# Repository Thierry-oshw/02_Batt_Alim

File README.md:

# 02_Batt_Alim

Le module Batt_Alim permet de gérer la charge d'une batterie Lipo constituée d'une seule cellule (4.2V) à partir d'une source de type 5V USB.
Il permet aussi de récupérer cette tension batterie variable et de reconstituer un 5V constant grâce à un DCDC.

La licence est celle du CERN Open Hardware Licence version 2; CERN-OHL-P ; permissive.
Le fichier de cette license est présent dans le répertoire: cern_ohl_p_v2.txt

# Photos

Ci-joint la photo de la version de 2021_06_04 // Here picture of version 2021_06_04:

# Schéma et fonctionnement

Ci-joint le schéma de la version de 2021_06_04 // Here schematic of version 2021_06_04:

Le module fonctionne de la façon suivante:
Il faut l'alimenter avec une tension 5V +-5% (typiquement celle de l'USB classique) sur la pin Vext. (Ne pas oublier GND bien sûr).

Il faut brancher la batterie Lipo sur V_bat+ et GND. La batterie Lipo doit être constituée d'une seule cellule, qui doit être chargée à 4.2V, présente une tension de 3.7V typique, et dont la tension de mise en protection est de 3V. La résistance R7 de 10kOhms permet de régler la puce TP4056 sur un courant de charge de 130mA. La batterie Lipo doit donc avoir une capacité d'au moins 2*130mAh, soit 260mAh au minimum. Plus d'information sur www.tp4056.com.

La sortie V_sum est à relier à DCDC_IN (ceci permet d'insérer un interrupteur à cet endroit).

La sortie 5V_p est une tension issue du DCDC qui est filtrée et protégée par la diode D1 et le condensateur C5.

La LED D6 indique la présence de 5V à la sortie du DCDC, avec "5V ON" comme étiquette.

Les LEDs D2 et D3 indiquent respectivement la charge et le mode standby du TP4056. Les étiquettes sont "CHG" et "STBY".

# Archives:

Ci-joint la photo de la version de 2020_12_22 // Here picture of version 2020_12_22:

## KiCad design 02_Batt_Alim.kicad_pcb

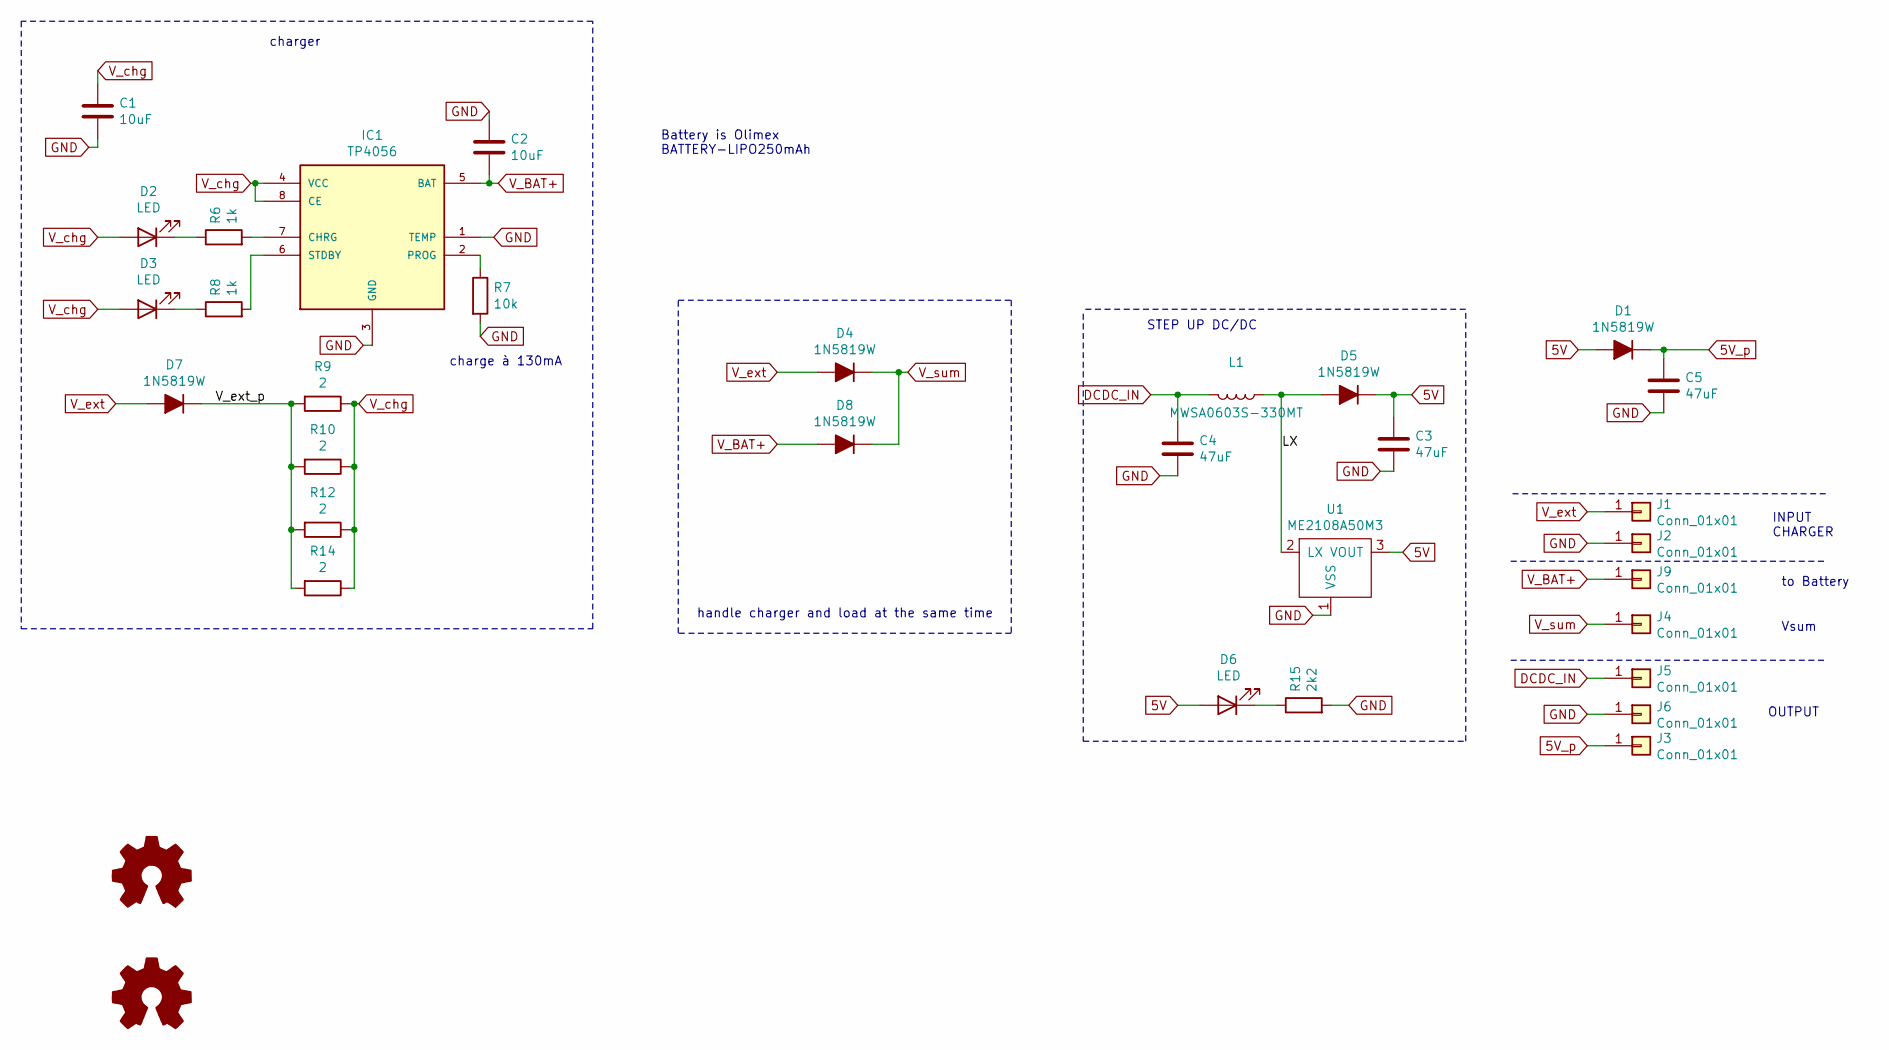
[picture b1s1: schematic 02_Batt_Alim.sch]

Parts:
C1, C2: 10uF; C_0603_1608Metric
C3, C4, C5: 47uF; C_1210_3225Metric
D1, D4, D5, D7, D8: 1N5819W; D_SOD-123F
D2, D3, D6: LED; D_0603_1608Metric
IC1: TP4056; SOP-8
J1, J2, J3, J4, J5, J6, J9: Conn_01x01; Castellated_conn
L1: MWSA0603S-330MT; L_Sunlord_MWSA0603S_6.6x7.0x2.8mm
R6, R8: 1k; R_0603_1608Metric
R7: 10k; R_0603_1608Metric
R9, R10, R12, R14: 2; R_0603_1608Metric
R15: 2k2; R_0603_1608Metric
U1: ME2108A50M3; SOT-23_Handsoldering

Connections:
5V: C3.1, D1.2 (A), D5.1 (K), D6.2 (A), U1.3 (VOUT)
5V_p: C5.1, D1.1 (K), J3.1
/LX: D5.2 (A), L1.1, U1.2 (LX)
/V_ext_p: D7.1 (K), R9.2, R10.2, R12.2, R14.2
DCDC_IN: C4.1, J5.1, L1.2
GND: C1.2, C2.1, C3.2, C4.2, C5.2, IC1.1 (TEMP), IC1.3 (GND), J2.1, J6.1, R7.2, R15.2, U1.1 (VSS)
unnamed: D2.1 (K), R6.1
unnamed: D3.1 (K), R8.1
unnamed: D6.1 (K), R15.1
unnamed: IC1.2 (PROG), R7.1
unnamed: IC1.6 (STDBY), R8.2
unnamed: IC1.7 (CHRG), R6.2
V_BAT+: C2.2, D8.2 (A), IC1.5 (BAT), J9.1
V_chg: C1.1, D2.2 (A), D3.2 (A), IC1.4 (VCC), IC1.8 (CE), R9.1, R10.1, R12.1, R14.1
V_ext: D4.2 (A), D7.2 (A), J1.1
V_sum: D4.1 (K), D8.1 (K), J4.1

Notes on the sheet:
Battery is Olimex BATTERY-LIPO250mAh
INPUT CHARGER
OUTPUT
STEP UP DC/DC
handle charger and load at the same time
charger
charge à 130mA
to Battery
Vsum

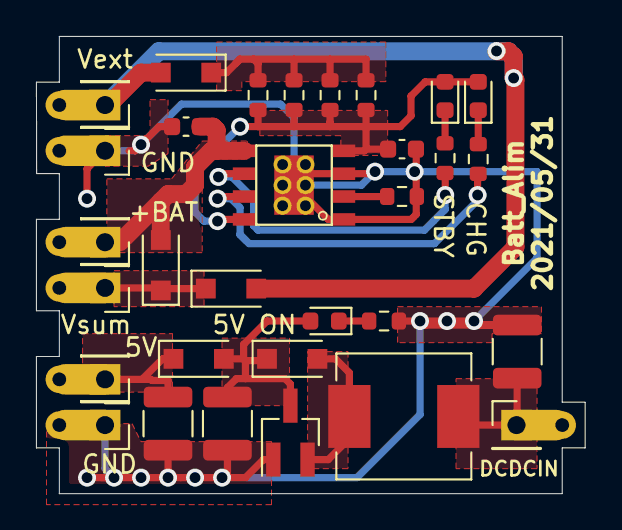
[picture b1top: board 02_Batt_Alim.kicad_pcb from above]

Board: 2 copper layers, 30.5 x 25.4 mm, 31 parts (0 on the bottom side), 16 nets.

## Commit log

2020-12-06 gitignore set to kicad version
2020-12-13 saisie du schéma + placement + premier routage
2020-12-14 dernières modification et routage avec plan de cuivre
2020-12-16 corrected diodes schematics; gerbers generation
2020-12-16 added kicad et oshw logos
2020-12-19 ajout logo kicad
2020-12-22 routage
2021-01-28 added picture
2021-02-06 simplify!
    1) battery lipo protection deleted
    2) move to schottky diodes instead of pmos for avoiding perturbation of charge while switch is on.
    3) reduced size of pcb
    4) added nmos for "hold" function
2021-02-22 simplification
    simplified the whole design
    Gerbers generated
2021-02-22 mechanical dimensions added
2021-05-21 coupé en deux
    séparé la partie dcdc du chargeur;
    schéma fait et routage en cours de modification
2021-05-28 modifications
    ajout diode + capa pour filtrer + protection en sortie
    changement inductance
2021-05-31 modifications
    - passage SOP8 en CMS
    - schéma correction ref 10k
2021-07-23 changed to new library
2021-07-23 changement librairie Chimère split
2021-09-07 maj fichier readme et images associées
2021-09-07 Update README.md
    description partie batterie améliorée.
2023-05-02 chgt nom fichier licence
